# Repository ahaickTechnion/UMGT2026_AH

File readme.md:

# UMGT ECU 2026

ESP32 DevKitC-32 + ESPSheild carrier board. Firmware lives in `UMGT/src/main.ino.cpp`
(PlatformIO, `pio run -e esp32dev`). Two GUIs:

- `ecu_dashboard.py` → `dist/ECU_Dashboard.exe` — low-level I/O test bench
- `engine_dashboard.py` → `dist/UMGT_Engine.exe` — **engine-run GUI**, ported
  from the LabVIEW `umgt_7thJuly2026.vi` test stand (see `LABVIEW_ANALYSIS.md`)

Build either exe: `pyinstaller --onefile --windowed --name <Name> <file>.py`.

All pin assignments below are verified against the KiCad netlist
(`UMGT/ESPSheild-KiCAD/ESPSheild.kicad_pcb`).

---

## ESP32 Pin Summary (verified)

| GPIO | Net | Function |
|------|-----|----------|
| GPIO1/3 | U0_TXD/U0_RXD | Serial 1 / USB console → EXE dashboard (J20) |
| GPIO2  | D2   | Extra I/O (J22) |
| GPIO4  | CRX  | **CAN RX** (SN65HVD230, J12) |
| GPIO5  | D5   | Extra I/O (J22) |
| GPIO12 | D12  | X9C digital pot **U/D** (J16) |
| GPIO13 | D13  | X9C digital pot **INC** (J16) |
| GPIO14 | D14  | Extra I/O (J22) |
| GPIO15 | D15  | Piezo / atomizer square wave (J19) |
| GPIO16 | U2_RXD | Serial 2 RX → Pixhawk (J21) |
| GPIO17 | U2_TXD | Serial 2 TX → Pixhawk (J21) |
| GPIO18 | SCK  | SPI clock (thermocouples) |
| GPIO19 | MISO | SPI MISO (thermocouples) |
| GPIO21 | SDA  | I2C data (PCF8575 expander @ 0x20) |
| GPIO22 | SCL  | I2C clock |
| GPIO23 | CTX  | **CAN TX** (no SPI MOSI on this board!) |
| GPIO25/26/27/32/33 | D25… | MOSFET PWM (J9, J10, J11, J7, J8) |
| GPIO34 | D34  | Analog: QNDB6 current sensor A (Battery) |
| GPIO35 | D35  | Analog: QNDB6 current sensor B (Load) |
| GPIO36/39 | VP/VN | Spare analog inputs (J24) |

## Thermocouples (MAX31855, SPI read-only)

Chip selects are **all on the PCF8575 expander** (active LOW).
Expander state bit = 8 + port number (P10 = bit 8 … P17 = bit 15).

| Connector | Net | Expander port | State bit | Channel |
|-----------|-----|---------------|-----------|---------|
| J3 | CS1 | P12 | 10 | TC1 — TIT |
| J4 | CS2 | P13 | 11 | TC2 — EGT |
| J5 | CS3 | P14 | 12 | TC3 — Bearing |
| J6 | CS4 | P15 | 13 | TC4 — Coil |

## Digital pot (X9C103S/X9C503S, J16)

| J16 pin | Signal | Driven by |
|---------|--------|-----------|
| 1 | GND | — |
| 2 | U/D | GPIO12 |
| 3 | INC | GPIO13 (wiper steps on falling edge) |
| 4 | CS  | Expander P16 (state bit 14, active LOW) |
| 5 | 3.3V | — |

Firmware resets the wiper to position 0 at boot and tracks it 0–99.

## MOSFET outputs (J7–J11, 2-pin GND+signal)

Verified wiring (2026-07-08):

| # | Connector | GPIO | Load |
|---|-----------|------|------|
| 1 | J7  | 32 | **Glow plug** (on/off) |
| 2 | J8  | 33 | **Solenoid 2** |
| 3 | J9  | 25 | **Solenoid 1** |
| 4 | J10 | 26 | **Fuel pump 2** (KNF 1.4-M) |
| 5 | J11 | 27 | **Fuel pump 1** (KNF 1.4-M) |

PWM: LEDC channels 2–6 (piezo has channel 0 on its own timer), duty 0–10,
shared frequency default 10 kHz.

## CAN / ESC (SN65HVD230, J12 / passthrough J18)

TWAI driver, TX=GPIO23, RX=GPIO4, default **1 Mbps** (DroneCAN standard).
The ESC is a **Hargrave microDRIVE LPi speaking DroneCAN (UAVCAN v0)**.
Firmware decodes:

- `uavcan.equipment.esc.Status` (1034, 10 Hz, multi-frame): RPM, bus voltage,
  bus current, bridge temperature, power %, plus Hargrave's custom 13-bit
  error field (over-temp, over/under-volt, sig loss, saturation, etc.)
- `uavcan.equipment.esc.StatusExtended` (1036, 1 Hz): input/output %,
  motor temperature, status flags

Decoded values stream as `ESC_RPM/ESC_V/ESC_I/ESC_T/ESC_PWR/ESC_ERR/ESC_AGE/
ESC_IN/ESC_OUT/ESC_MT` keys and fill the ESC banner in the exe. `can esc`
prints them on demand with error names spelled out.

ESC control (all repeated at 50 Hz as node 100, array padded to the ESC's
reported index; `can stop` ends any mode with an explicit zero):

- `can duty <-100..100>` — duty cycle via `esc.RawCommand` (1030). Negative
  duty needs the ESC's **Reversible** drive mode (Normal mode clamps to 0).
- `can rpm <setpoint>` — closed-loop RPM via `esc.RPMCommand` (1031); the ESC
  clamps to its configured min/max RPM (needs correct pole-pair setting).
- `can brake <0-100>` — regen braking as negative duty (Reversible mode);
  braking torque is capped by the ESC's bus/phase current-limit settings.

The commanded mode/value streams back as `ESC_CMODE`/`ESC_CVAL` so the exe
always shows what is being commanded. The codec (Status, StatusExtended RX;
RawCommand, RPMCommand TX, negatives included) was verified bit-exact against
the reference `dronecan` python library.

The ECU is also a **dynamic node ID allocation server** (the role an autopilot
normally plays): an ESC with no node ID sends anonymous allocation requests,
the ECU collects its 16-byte unique ID over the 3-stage exchange and grants it
an ID (its preference, else 125). The ECU broadcasts its own NodeStatus at
1 Hz as node 100. Decoded NodeStatus heartbeats and anonymous-request counts
stream as `NS_ID/NS_MODE/NS_HP/NS_UP` and `ANON`, and the exe Bus tile shows
the allocation state (NO ID → NODE n → ESC OK). The allocation wire format
(echo + multi-frame CRC grant) was verified against pydronecan.

## Current sensors (QNDB6 hall, 100A / 5V output)

GPIO34 = Battery, GPIO35 = Load. Default calibration 20 A/V, zero at 0 V
(`current cal <zeroV> <A_per_V>` to adjust). Note: the ESP32 ADC clips at
~3.3 V ≈ 66 A unless a divider is added.

## Expander extra I/O

P00–P07 (state bits 0–7) are broken out on J13/J17 "EXTRA IO EXPAND" and are
controllable with `i2c expander bit <n> on|off`.

---

## Serial command set (115200 baud on USB)

```
status                          full status dump
tc read <1-4|all>               thermocouples (1=TIT 2=EGT 3=Bearing 4=Coil)
tc scan                         probe all 16 expander CS bits (find wiring/CS issues)
tc mode 31855|6675              select thermocouple chip decode
current all|a|b                 current sensors in amps
current cal <zeroV> <A_per_V>   calibration
pot pos|up <n>|down <n>|set <0-99>|reset|store
can [status|esc]                bus status + decoded microDRIVE telemetry
can duty <-100..100>            duty command (RawCommand 1030, 50 Hz)
can rpm <setpoint>              closed-loop RPM (RPMCommand 1031, 50 Hz)
can brake <0-100>               regen brake = negative duty (Reversible mode)
can stop                        stop any ESC command, send zero
can param list                  enumerate all ESC settings (99 on microDRIVE LPi)
can param get|set <NAME> [v]    by name — CASE-SENSITIVE (e.g. BUS_CUR_LIM)
can param geti|seti <idx> [v]   by index (typed automatically after a read)
can save                        persist ESC params to NVM (microDRIVE reboots itself)
can restart                     reboot ESC (clears latched ERROR flags)
can baud <125|250|500|1000> | can send <id> <hex bytes> | can print on|off
mosfet all|<1-5> on|off|duty <0-10>   ·   mosfet freq <hz>
piezo on|off|duty <0-255>|freq <hz>
analog all|vp|vn|a|b            raw ADC + volts
i2c scan | i2c expander set <hex> | i2c expander bit <n> on|off
serial2 send <text>             forward to Pixhawk UART
serial2 baud <rate>             change Serial2 baud (Pixhawk telem is usually 57600)
serial2 hex on|off              hex-dump Serial2 traffic (MAVLink is binary)
stream on|off                   telemetry stream (default 10 Hz)
stream rate <1-50>              stream rate in Hz; TCs sample at a fixed 10 Hz
                                (MAX31855 converts internally every ~100 ms)
```

### Engine control (ported from LabVIEW + designed sequencer)

```
eng start                       auto sequence: PRECHECK→GLOW→SPOOL→IGNITION→WARMUP→RUNNING
eng stop                        normal shutdown: fuel+glow off → COOLDOWN spin → OFF
eng abort | eng reset           immediate kill (latched FAULT) / clear fault
eng manual                      manual mode (direct pump/glow/throttle, failsafes live)
eng status | eng params         status dump / list parameters (PARAM:name=value)
eng set <name> <value>          edit any sequence/limit/PID parameter (live RAM)
eng save | eng defaults         persist params to ECU flash (survives reboot) / clear
gov on|off | gov sp <rpm>       RPM governor (NI PID Advanced form, out 15-100%)
gov gains <kc> <ti_min> <td_min>
thr <0-100>                     manual engine throttle (slew via governor off)
ramp up|down|pause|off          LabVIEW-style throttle ramp; ramp rate <pct/s>
pump <1|2> <0-100>              independent KNF fuel pumps, fine PWM; pump stop
glow on|off                     glow plug on MOSFET M1 (GPIO32)
sol <1|2> on|off                solenoid 1 (M3/GPIO25) / 2 (M2/GPIO33)
fuel cut on|off                 fuel shutoff latch (pumps forced to 0)
```

Failsafes (always active when anything is live, all editable):
TIT/coil/bearing over-temp, overspeed, flameout (lit + fuel + TIT below
floor), ESC telemetry loss, TIT thermocouple loss mid-sequence. Any trip →
everything safe + latched FAULT.

Engine stream keys: `ENG,FLT,GLW,P1,P2,FF,GOV,GSP,THR,FCUT,RMP`; state
transitions and faults print as `ENG:STATE=…` / `ENG:FAULT=…` events.

Actuators: glow=M1(32), sol2=M2(33), sol1=M3(25), pump2=M4(26), pump1=M5(27),
ESC=DroneCAN. Sensors: TC1=TIT, TC2=glow area, TC3=bearing, TC4=coil,
RPM/V/I from ESC.

Stream line format:

```
DATA:TC1=..,TC2=..,TC3=..,TC4=..,I_A=..,I_B=..,AVP=..,AVN=..,POT=..,PZF=..,PZD=..,CANRX=..,M1=..,..,M5=..
```

`HB` is emitted every second as a heartbeat; Pixhawk traffic is bridged to the
console as `[Serial2] …` lines.

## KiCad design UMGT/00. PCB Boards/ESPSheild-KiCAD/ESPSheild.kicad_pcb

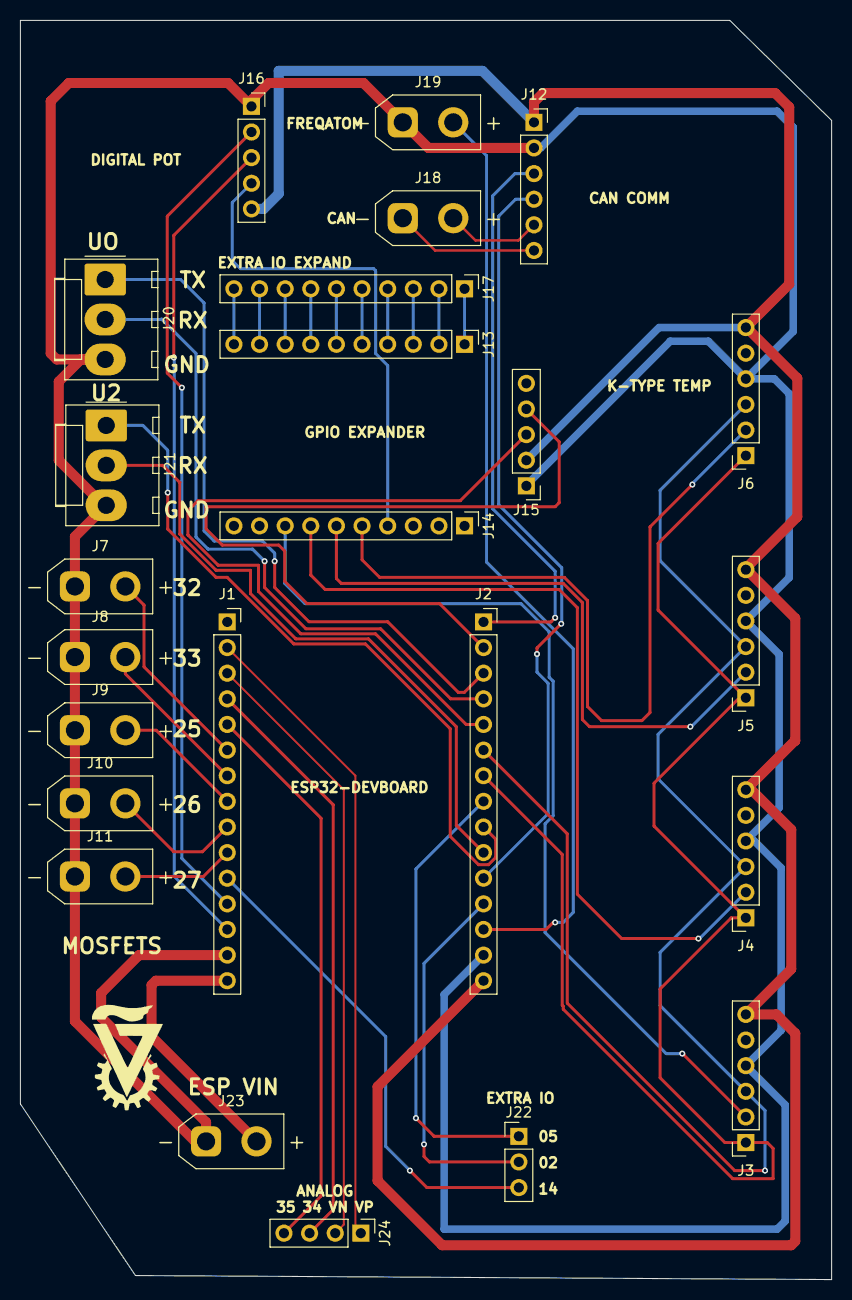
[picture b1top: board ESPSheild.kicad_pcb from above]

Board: 2 copper layers, 80.4 x 124.8 mm, 25 parts (0 on the bottom side), 45 nets.

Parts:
J1, J2: Conn_01x15; PinSocket_1x15_P2.54mm_Vertical
J3, J4, J5, J6, J12: Conn_01x06; PinSocket_1x06_P2.54mm_Vertical
J7, J8, J9, J10, J11, J18, J19, J23: Conn_01x02; AMASS_XT30UPB-M_1x02_P5.0mm_Vertical
J13, J14, J17: Conn_01x10; PinHeader_1x10_P2.54mm_Vertical
J15: Conn_01x05; PinHeader_1x05_P2.54mm_Vertical
J16: Conn_01x05; PinSocket_1x05_P2.54mm_Vertical
J20, J21: Conn_01x03; Molex_KK-396_A-41791-0003_1x03_P3.96mm_Vertical
J22: Conn_01x03; PinHeader_1x03_P2.54mm_Vertical
J24: Conn_01x04; PinHeader_1x04_P2.54mm_Vertical
g**: LOGO

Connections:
3.3V: J2.15, J3.6, J4.6, J5.6, J6.6, J12.1, J15.2, J16.5
CANH: J12.5, J18.2
CANL: J12.6, J18.1
CRX: J2.11, J12.4
CS1: J3.2, J14.8
CS2: J4.2, J14.7
CS3: J5.2, J14.6
CS4: J6.2, J14.5
CS5: J14.4, J16.4
CTX: J2.1, J12.3
D2: J2.12, J22.2
D5: J2.8, J22.1
D12: J1.12, J16.2
D13: J1.13, J16.3
D14: J1.11, J22.3
D15: J2.13, J19.2
D25: J1.8, J9.2
D26: J1.9, J10.2
D27: J1.10, J11.2
D32: J1.6, J7.2
D33: J1.7, J8.2
D34: J1.4, J24.3
D35: J1.5, J24.4
GND: J1.14, J2.14, J3.4, J4.4, J5.4, J6.4, J7.1, J8.1, J9.1, J10.1, J11.1, J12.2, J15.1, J16.1, J19.1, J20.3, J21.3, J23.1
MISO: J2.6, J3.3, J4.3, J5.3, J6.3
unnamed: J13.1, J17.1
unnamed: J13.2, J17.2
unnamed: J13.3, J17.3
unnamed: J13.4, J17.4
unnamed: J13.5, J17.5
unnamed: J13.6, J17.6
unnamed: J13.7, J17.7
unnamed: J13.8, J17.8
unnamed: J13.9, J17.9
unnamed: J13.10, J17.10
SCK: J2.7, J3.1, J4.1, J5.1, J6.1
SCL: J2.2, J15.4
SDA: J2.5, J15.3
U2_RXD: J2.10, J21.2
U2_TXD: J2.9, J21.1
UO_RXD: J2.4, J20.2
UO_TXD: J2.3, J20.1
VIN: J1.15, J23.2
VN: J1.3, J24.2
VP: J1.2, J24.1

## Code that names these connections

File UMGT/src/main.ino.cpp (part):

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
// Pixhawk MAVLink UART on J21 / SERIAL 2 (U2). Solid keyed 3-pin connector.
//   Cube TELEM1 TX (pin 2) -> U2 RX (GPIO16),  Cube RX (pin 3) -> U2 TX (GPIO17).
#define PIN_UART2_RX      16   // U2_RXD (J21)
#define PIN_UART2_TX      17   // U2_TXD (J21)

// CAN / TWAI → ESC via SN65HVD230 on J12 (3V3, GND, CTX, CRX, CANH, CANL)
// The ESC is a Hargrave microDRIVE LPi speaking DroneCAN (UAVCAN v0),
// standard bitrate 1 Mbps.
#define PIN_CAN_TX        23   // net CTX (J2 pad 1)
#define PIN_CAN_RX        4    // net CRX (J2 pad 11)
#define CAN_DEFAULT_KBPS  1000

// DroneCAN identifiers
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
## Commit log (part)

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2026-06-07 first files
2026-06-07 added pin assign
2026-06-07 added plat
2026-06-09 added starter code for the main
2026-06-11 added correct mosfet control
2026-06-28 added kicad files
2026-06-29 added exe
